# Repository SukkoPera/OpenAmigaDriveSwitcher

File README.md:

# OpenAmigaDriveSwitcher
OpenAmigaDriveSwitcher is an Open Hardware adapter that can make the first external floppy disk drive (*DF1:*) on an Amiga 500/500+ appear in place of the internal drive (*DF0:*). It also works on an Amiga 2000, however *DF1:* is still an internal drive on this computer.

### Summary
OpenAmigaDriveSwitcher turns out really handy for people using a Gotek floppy drive emulator who don't want to mount it internally. In fact, this requires some case modding, both for fitting the drive and for making it useable, as having a display on the side of the Amiga is quite uncomfortable. Connecting the Gotek externally will not work out of the box for most games as they assume they are running on *DF0:*, which was the only bootable drive back in AmigaOS 1.x times.

Keeping a Gotek drive external also allows it to be used with different computers.

OpenAmigaDriveSwitcher comes as an adapter PCB that sits between the Even CIA chip and its socket and can make the external drive appear as *DF0:*. However, it does not fully *swap* the drives, which means that when it is enabled, **the internal drive just "disappears"**, it does NOT become *DF1:*.

### Assembly
Solder the 74LS157 chip and its decoupling capacitor first. Do not use a socket for it, as it will be sitting underneath the CIA. Before soldering, you might want to make sure that the socket for the CIA chip sits properly in its place, as everything will be quite crammed. You can bend the legs of the chip slightly to that it is offset a bit to the right, where more space is available.

Then solder the pins that will plug in the original socket.

Use a 48-pin (or 2x24-pin) socket for the CIA, and solder it last.

NOTE: You can use a 74LS257 in place of the the 157, if you have one handy. Recommended logic families are *LS* and *HCT*, but *HC* might work as well.

### Installation
Installation of the adapter is straightforward: carefully replace your EVEN CIA chip with the adapter and plug the CIA on it. Just make sure to respect the orientation.

Currently, the device has been tested and found working on A500, A500+ and A2000. In all cases, when the device is installed, you will still be able to place the metal shield (if applicable) and close the case properly.

To control OpenAmigaDriveSwitcher you have several choices. The simplest solution is to use a SPDT switch, which can either be installed into the back of the case by drilling a small hole or be left wandering in the trapdoor slot, at the user's preference (at least on A500s). It can either be connected to the header pins or soldered to the available pads, they are equivalent.

But the real strength of OpenAmigaDriveSwitcher is that it can be driven with a logic signal, since it uses a 74157 to switch the required lines. This means you can avoid drilling a hole in your precious case and rather use some electronic means to generate the switch signal.

For instance, the signal can come from an [OpenAmigaMouseTrigger](https://github.com/SukkoPera/OpenAmigaMouseTrigger) detecting mouse presses when the Amiga is powered on: you just turn on your Amiga while holding LMB and *DF1:* becomes *DF0:*.

Another possibility is to wire a microcontroller to the keyboard lines and detect a particular keypress, such as the reset combo. A simple sketch to be loaded on an Arduino for this purpose is provided: you keep the reset combo pressed for two seconds and *DF1:* becomes *DF0:*, you don't even need to power off your Amiga!

I'm sure you can come up with more ideas :).

### License
The OpenAmigaDriveSwitcher documentation, including the design itself, is copyright &copy; SukkoPera 2018.

OpenAmigaDriveSwitcher is Open Hardware licensed under the [CERN OHL v. 1.2](http://ohwr.org/cernohl).

You may redistribute and modify this documentation under the terms of the CERN OHL v.1.2. This documentation is distributed *as is* and WITHOUT ANY EXPRESS OR IMPLIED WARRANTIES whatsoever with respect to its functionality, operability or use, including, without limitation, any implied warranties OF MERCHANTABILITY, SATISFACTORY QUALITY, FITNESS FOR A PARTICULAR PURPOSE or infringement. We expressly disclaim any liability whatsoever for any direct, indirect, consequential, incidental or special damages, including, without limitation, lost revenues, lost profits, losses resulting from business interruption or loss of data, regardless of the form of action or legal theory under which the liability may be asserted, even if advised of the possibility or likelihood of such damages.

A copy of the full license is included in file [LICENSE.pdf](LICENSE.pdf), please refer to it for applicable conditions. In order to properly deal with its terms, please see file [LICENSE_HOWTO.pdf](LICENSE_HOWTO.pdf).

The contact points for information about manufactured Products (see section 4.2) are listed in file [PRODUCT.md](PRODUCT.md).

Any modifications made by Licensees (see section 3.4.b) shall be recorded in file [CHANGES.md](CHANGES.md).

The Documentation Location of the original project is https://github.com/SukkoPera/OpenAmigaDriveSwitcher/.

### Support the Project
Since the project is open you are free to get the PCBs made by your preferred manufacturer, however in case you want to support the development, you can order them from PCBWay through this link:

You get cheap, professionally-made and good quality PCBs, I get some credit that will help with this and [other projects](https://www.pcbway.com/project/member/shareproject/?bmbid=41100). You won't even have to worry about the various PCB options, it's all pre-configured for you!

Also, if you still have to register to that site, [you can use this link](https://www.pcbway.com/setinvite.aspx?inviteid=41100) to get some bonus initial credit (and yield me some more).

Again, if you want to use another manufacturer, feel free to, don't feel obligated :).

### Get Help
If you need help or have any questions, you can join [the official Telegram group](https://t.me/joinchat/HUHdWBC9J9JnYIrvTYfZmg).

### Thanks
- The fundamental method to swap the drives was learnt from [this thread](http://eab.abime.net/showthread.php?t=89581) by user *Lurch_AU* of the EAB forum.

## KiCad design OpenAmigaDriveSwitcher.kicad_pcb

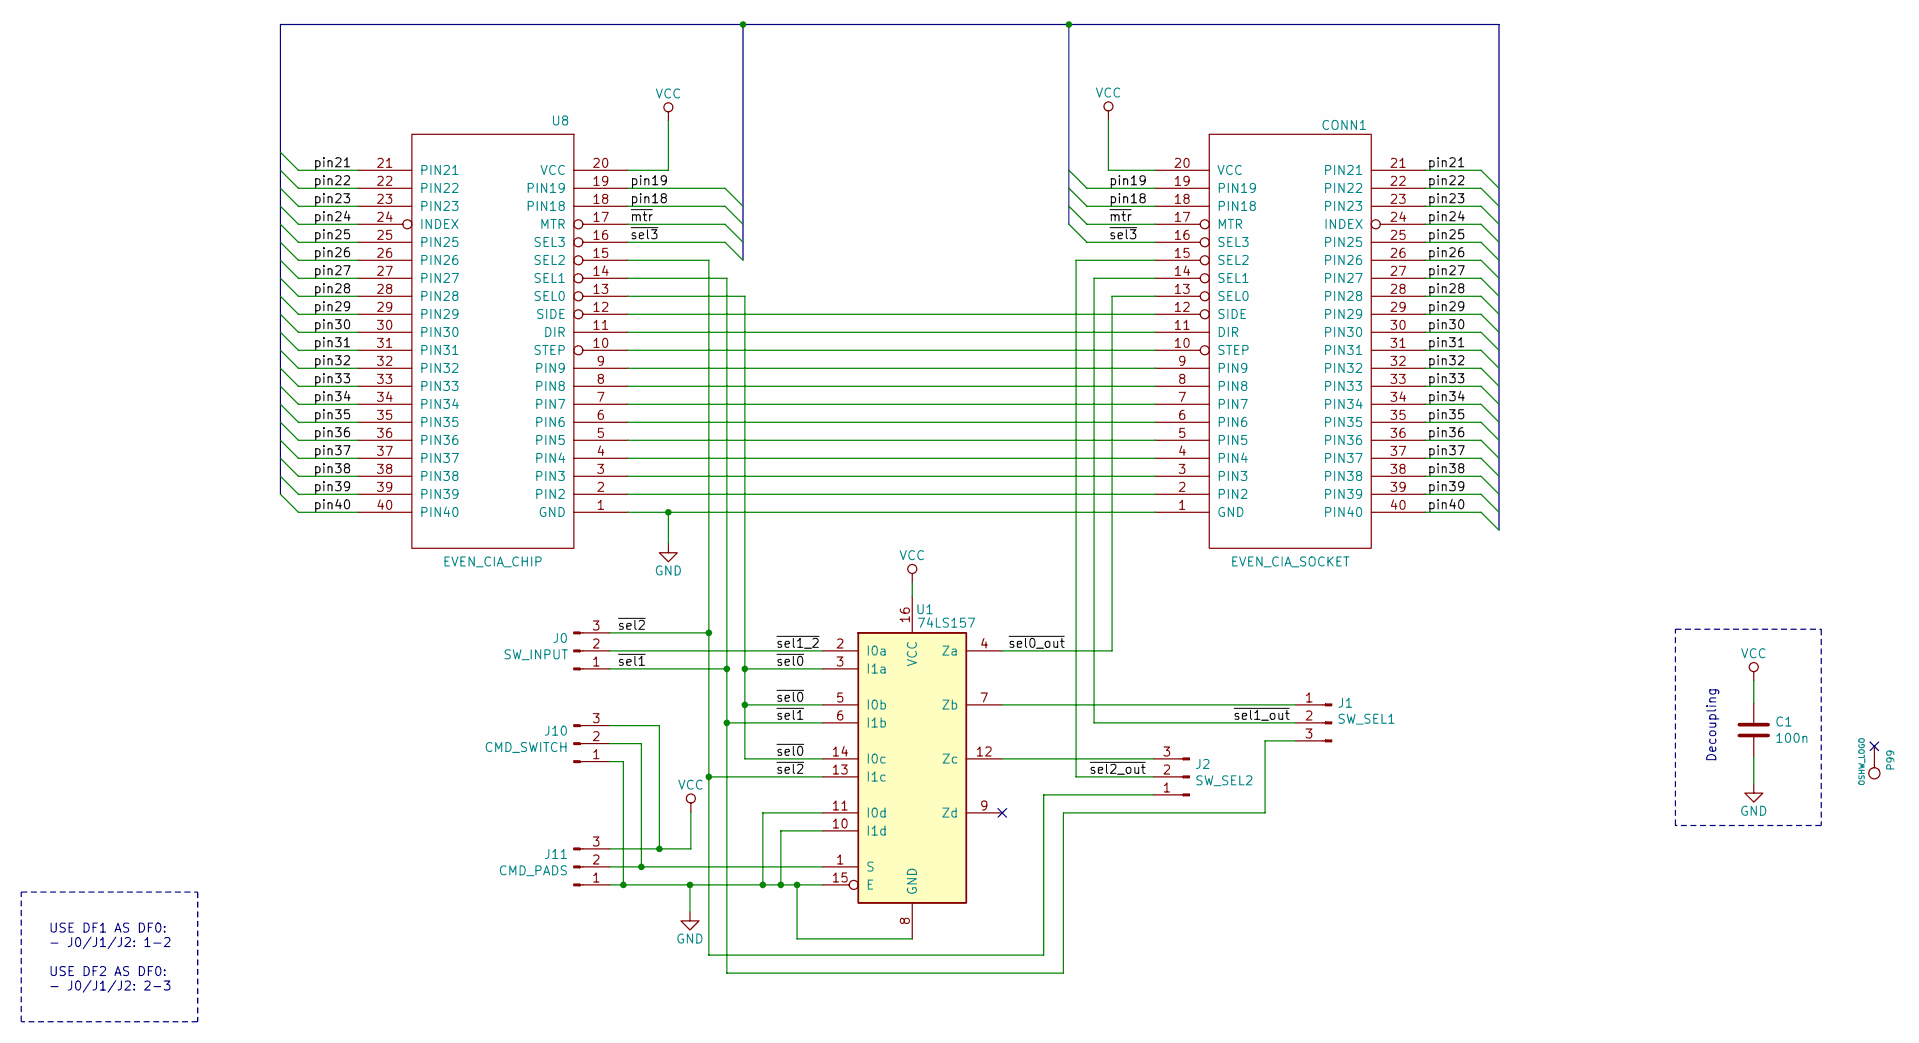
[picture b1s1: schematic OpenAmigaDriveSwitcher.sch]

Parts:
C1: 100n; C_Disc_D7.0mm_W2.5mm_P5.00mm
CONN1: EVEN_CIA_SOCKET; DIP-40_DualHeaderStrips
J0: SW_INPUT; SolderJumper-3_P1.3mm_Bridged12_RoundedPad1.0x1.5mm
J1: SW_SEL1; SolderJumper-3_P1.3mm_Bridged12_RoundedPad1.0x1.5mm
J2: SW_SEL2; SolderJumper-3_P1.3mm_Bridged12_RoundedPad1.0x1.5mm
J10: CMD_SWITCH; Pin_Header_Straight_1x03-ModSilkS
J11: CMD_PADS; SolderJumper3
P99: OSHW_LOGO; OSHW-Logo_5.7x6mm_Copper
U1: 74LS157; DIP-16_W7.62mm
U8: EVEN_CIA_CHIP; DIP-40_Socket

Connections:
/pin18: CONN1.18 (PIN18), U8.18 (PIN18)
/pin19: CONN1.19 (PIN19), U8.19 (PIN19)
/pin21: CONN1.21 (PIN21), U8.21 (PIN21)
/pin22: CONN1.22 (PIN22), U8.22 (PIN22)
/pin23: CONN1.23 (PIN23), U8.23 (PIN23)
/pin24: CONN1.24 (INDEX), U8.24 (INDEX)
/pin25: CONN1.25 (PIN25), U8.25 (PIN25)
/pin26: CONN1.26 (PIN26), U8.26 (PIN26)
/pin27: CONN1.27 (PIN27), U8.27 (PIN27)
/pin28: CONN1.28 (PIN28), U8.28 (PIN28)
/pin29: CONN1.29 (PIN29), U8.29 (PIN29)
/pin30: CONN1.30 (PIN30), U8.30 (PIN30)
/pin31: CONN1.31 (PIN31), U8.31 (PIN31)
/pin32: CONN1.32 (PIN32), U8.32 (PIN32)
/pin33: CONN1.33 (PIN33), U8.33 (PIN33)
/pin34: CONN1.34 (PIN34), U8.34 (PIN34)
/pin35: CONN1.35 (PIN35), U8.35 (PIN35)
/pin36: CONN1.36 (PIN36), U8.36 (PIN36)
/pin37: CONN1.37 (PIN37), U8.37 (PIN37)
/pin38: CONN1.38 (PIN38), U8.38 (PIN38)
/pin39: CONN1.39 (PIN39), U8.39 (PIN39)
/pin40: CONN1.40 (PIN40), U8.40 (PIN40)
/~mtr: CONN1.17 (MTR), U8.17 (MTR)
/~sel0: U1.3 (I1a), U1.5 (I0b), U1.14 (I0c), U8.13 (SEL0)
/~sel0_out: CONN1.13 (SEL0), U1.4 (Za)
/~sel1: J0.1, J1.3, U1.6 (I1b), U8.14 (SEL1)
/~sel1_2: J0.2, U1.2 (I0a)
/~sel1_out: CONN1.14 (SEL1), J1.2
/~sel2: J0.3, J2.1, U1.13 (I1c), U8.15 (SEL2)
/~sel2_out: CONN1.15 (SEL2), J2.2
/~sel3: CONN1.16 (SEL3), U8.16 (SEL3)
GND: C1.2, CONN1.1 (GND), J10.1, J11.1, U1.8 (GND), U1.10 (I1d), U1.11 (I0d), U1.15 (E), U8.1 (GND)
unnamed: CONN1.2 (PIN2), U8.2 (PIN2)
unnamed: CONN1.3 (PIN3), U8.3 (PIN3)
unnamed: CONN1.4 (PIN4), U8.4 (PIN4)
unnamed: CONN1.5 (PIN5), U8.5 (PIN5)
unnamed: CONN1.6 (PIN6), U8.6 (PIN6)
unnamed: CONN1.7 (PIN7), U8.7 (PIN7)
unnamed: CONN1.8 (PIN8), U8.8 (PIN8)
unnamed: CONN1.9 (PIN9), U8.9 (PIN9)
unnamed: CONN1.10 (STEP), U8.10 (STEP)
unnamed: CONN1.11 (DIR), U8.11 (DIR)
unnamed: CONN1.12 (SIDE), U8.12 (SIDE)
unnamed: J1.1, U1.7 (Zb)
unnamed: J2.3, U1.12 (Zc)
unnamed: J10.2, J11.2, U1.1 (S)
VCC: C1.1, CONN1.20 (VCC), J10.3, J11.3, U1.16 (VCC), U8.20 (VCC)

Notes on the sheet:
Decoupling
USE DF1 AS DF0: - J0/J1/J2: 1-2 USE DF2 AS DF0: - J0/J1/J2: 2-3

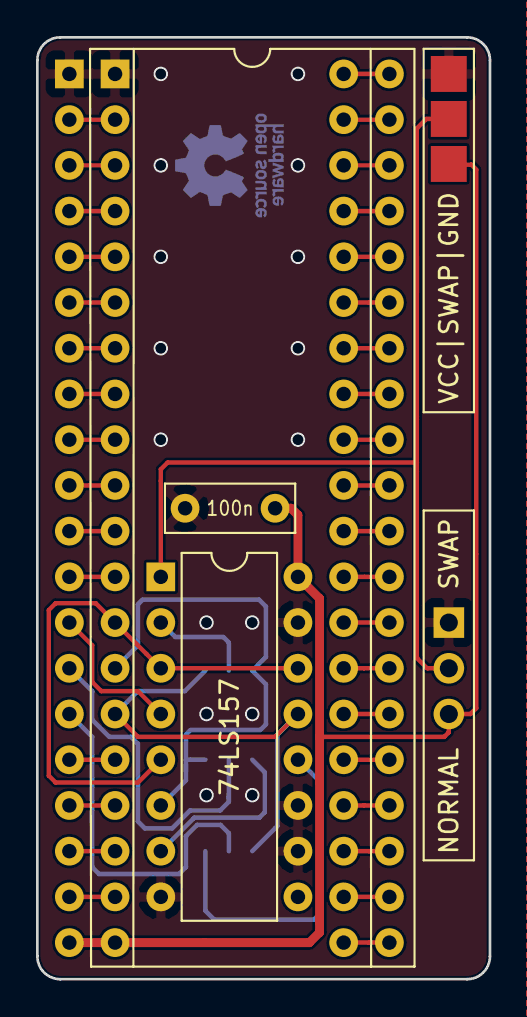
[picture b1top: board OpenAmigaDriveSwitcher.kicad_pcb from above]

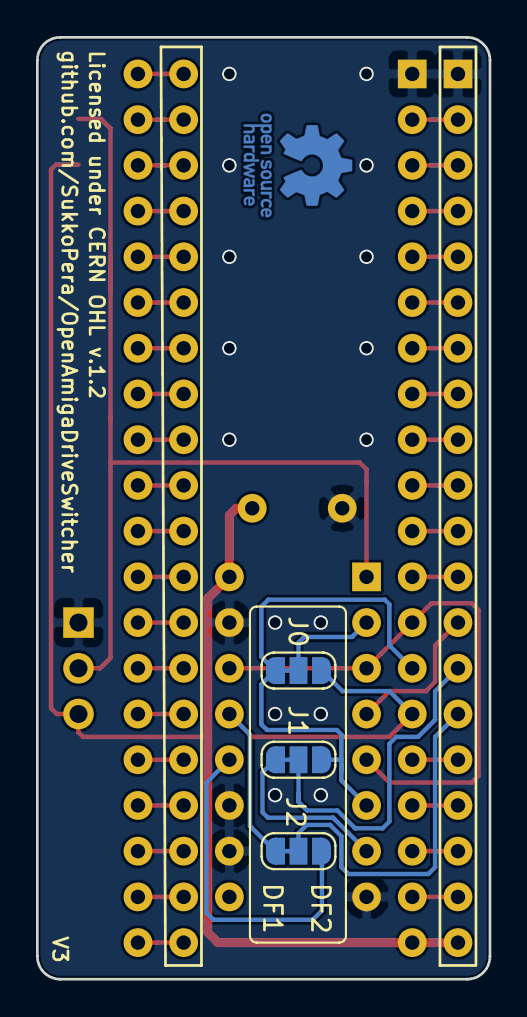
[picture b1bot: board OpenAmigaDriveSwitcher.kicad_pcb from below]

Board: 2 copper layers, 25.1 x 52.3 mm, 10 parts (4 on the bottom side), 47 nets.

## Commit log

2018-06-26 Add .gitignore
2018-06-26 Ready for V1
2018-06-26 Add version number
2018-08-18 V2: Reverse swap pin logic (i.e: swap drives when it is grounded) This will make the switcher more easily controllable by OpenAmigaMouseTrigger. Also migrate project to KiCad 5.
2018-08-18 Remove legacy KiCad 4 symbols
2018-08-18 Fix and improve silkscreen
2018-08-18 Minor fix
2018-09-13 Reduce clearance
2018-09-13 Allow swapping DF0 <-> DF2
2018-11-19 Add README
2018-11-19 Add renders
2018-11-19 Crop renders
2018-11-19 Fix typo
2018-11-19 Add credits
2018-12-10 Add CERN OHL v.1. 2
2018-12-10 Rename license files
2018-12-10 Add OHL claim
2018-12-10 Ready for V3

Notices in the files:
OpenAmigaDriveSwitcher.kicad_pcb:
Licensed under CERN OHL v.1.2
